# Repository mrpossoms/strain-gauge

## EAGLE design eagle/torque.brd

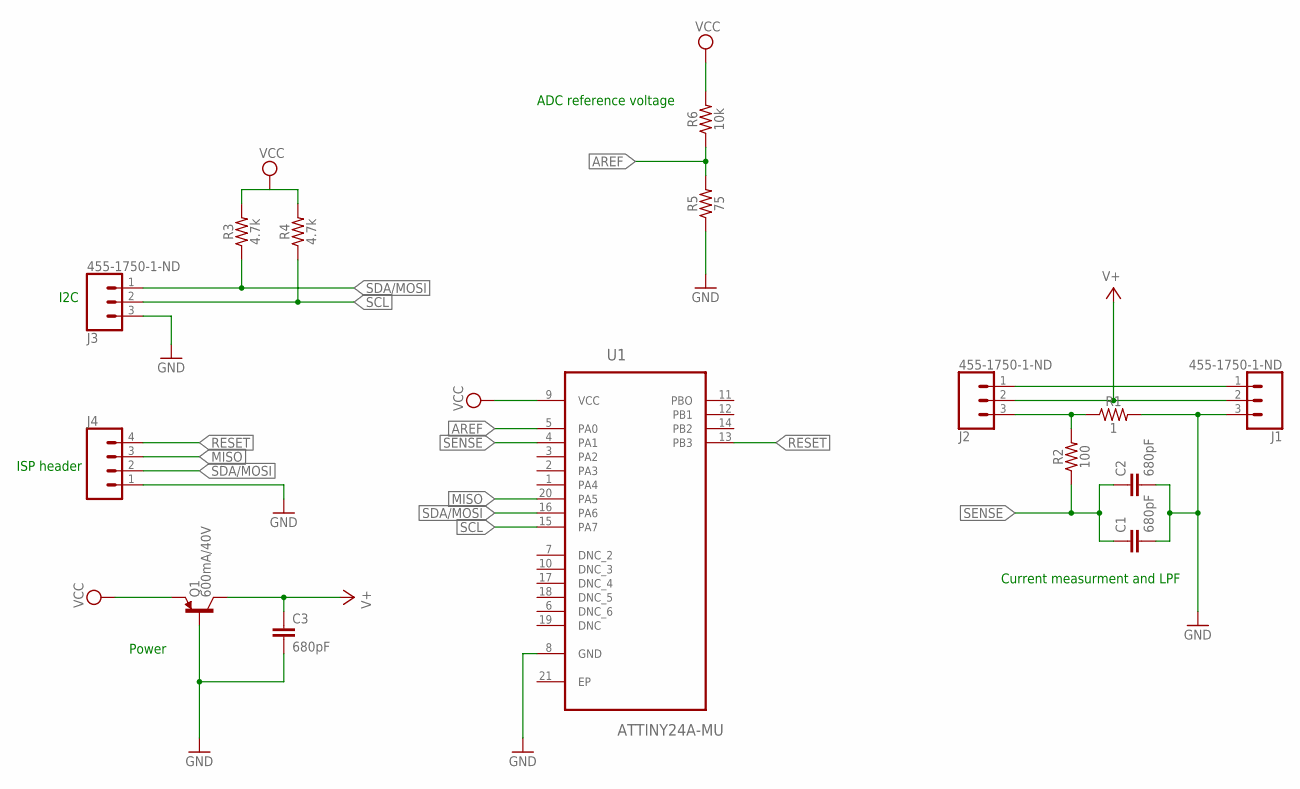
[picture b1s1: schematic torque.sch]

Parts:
C1, C2, C3: 680pF; 0603
J1, J2, J3: 455-1750-1-ND; 1X03
J4: CONN_04SMD_RA_FEMALE; 1X04_SMD_RA_FEMALE
Q1: 600mA/40V; SOT23-3
R1: 1; 0603
R2: 100; 0603
R3, R4: 4.7k; 0603
R5: 75; 0603
R6: 10k; 0603
U1: ATTINY24A-MU; QFN50P400X400X80-21N

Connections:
AREF: R5.2, R6.1, U1.5 (PA0)
GND: C1.2, C2.2, C3.2, J1.3, J3.3, J4.1, Q1.1 (B), R1.2, R5.1, U1.8 (GND)
MISO: J4.3, U1.20 (PA5)
unnamed: J2.3, R1.1, R2.2
unnamed: J1.1, J2.1
unnamed: R3.2, R4.2
RESET: J4.4, U1.13 (PB3)
SCL: J3.2, R4.1, U1.15 (PA7)
SDA/MOSI: J3.1, J4.2, R3.1, U1.16 (PA6)
SENSE: C1.1, C2.1, R2.1, U1.4 (PA1)
V+: C3.1, J1.2, J2.2, Q1.3 (C)
VCC: Q1.2 (E), R6.2, U1.9 (VCC)

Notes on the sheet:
ADC reference voltage
Current measurment and LPF
Power
ISP header
I2C

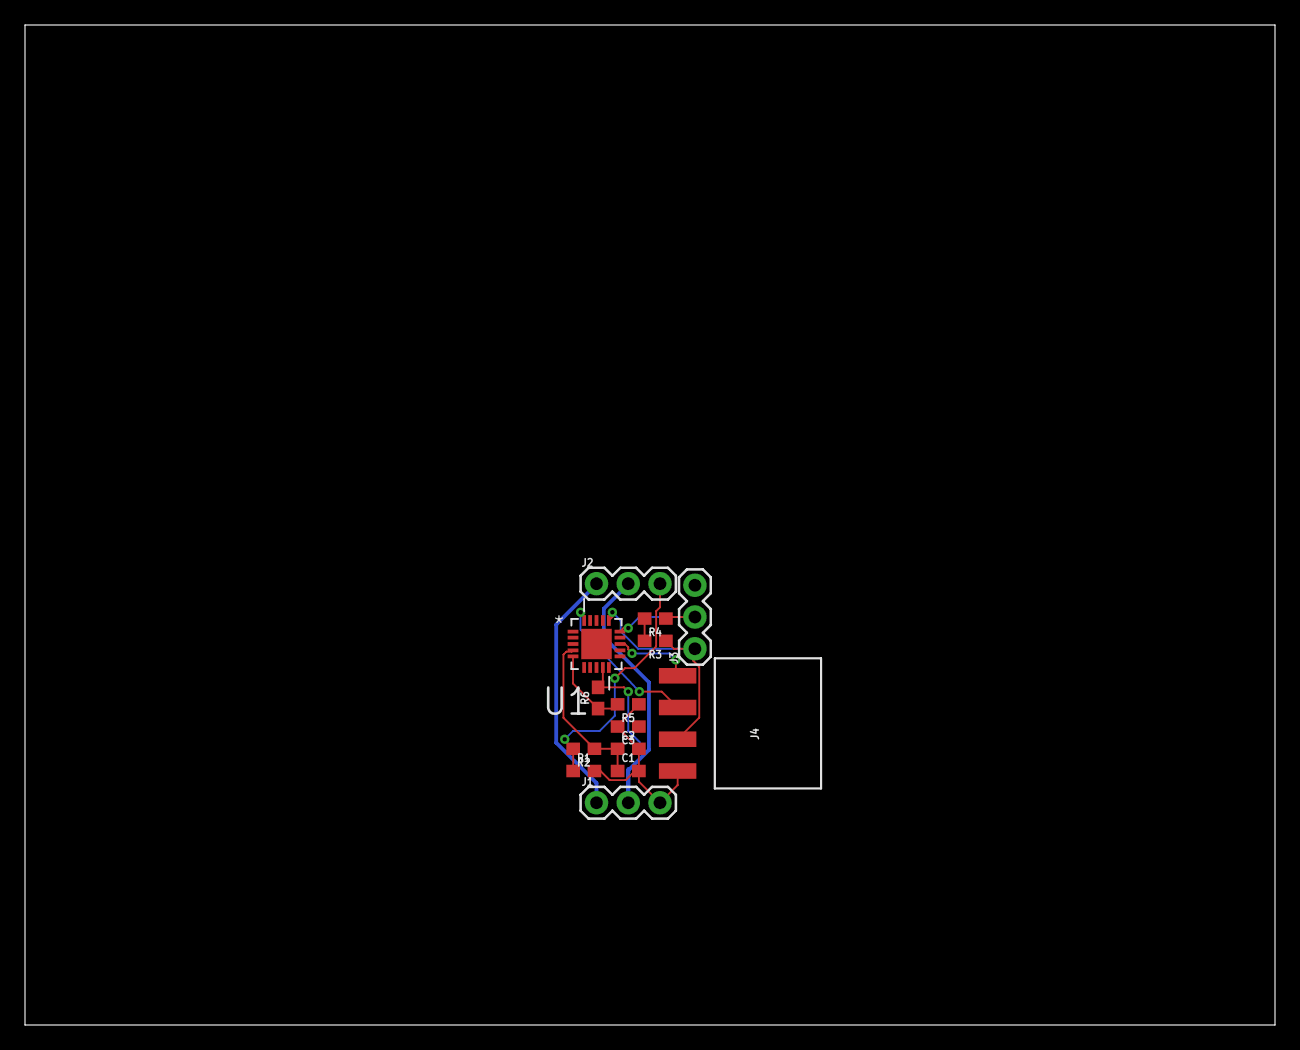
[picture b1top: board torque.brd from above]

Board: 2 copper layers, 100.0 x 80.0 mm, 15 parts (1 on the bottom side), 12 nets.

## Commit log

2018-09-24 Started working on firmware

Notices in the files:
parts and their libraries:
SparkFun-Capacitors: Licensing: Creative Commons ShareAlike 4.0 International - https://creativecommons.org/licenses/by-sa/4.0
